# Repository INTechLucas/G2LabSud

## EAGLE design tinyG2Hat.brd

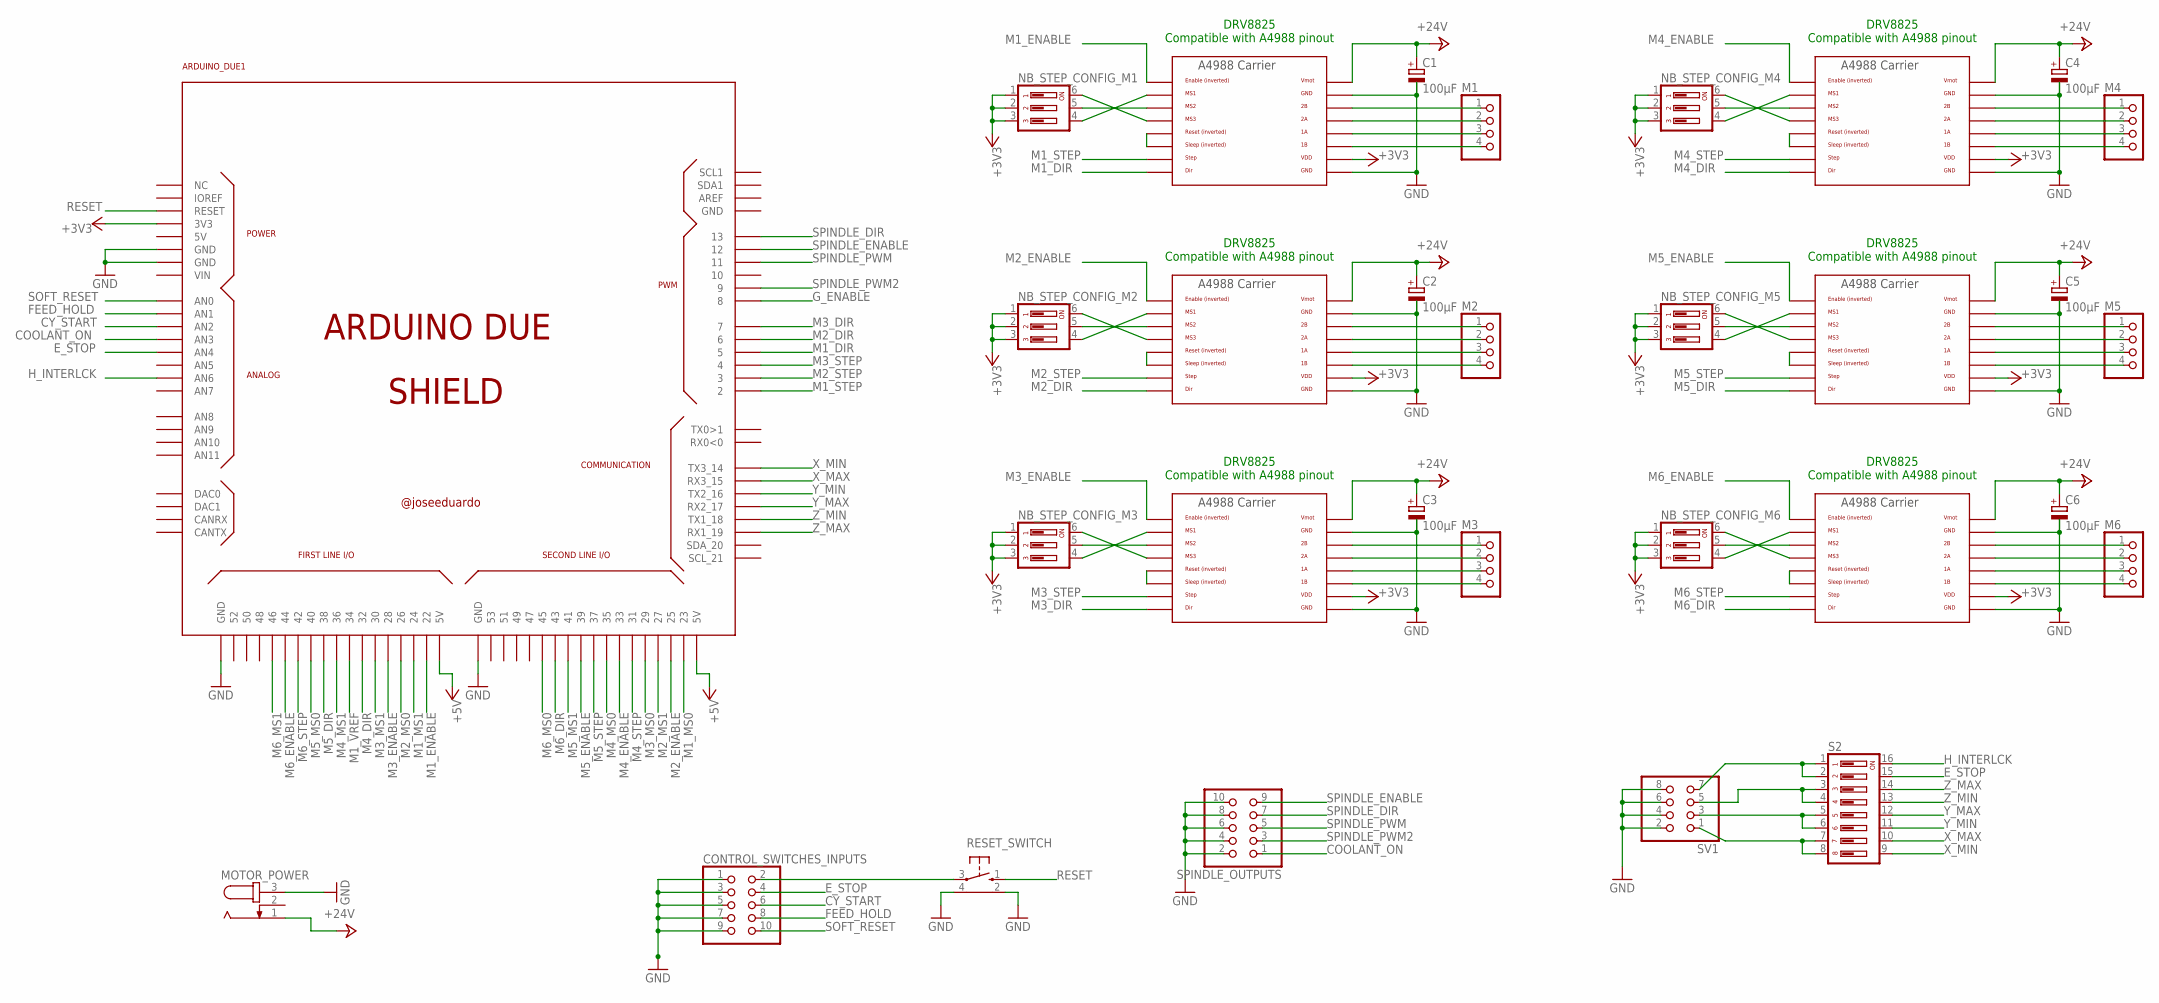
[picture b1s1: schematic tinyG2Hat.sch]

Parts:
ARDUINO_DUE1: ARDUINO_DUE_SHIELD_NOSPI
C1, C2, C3, C4, C5, C6: 100µF; E3,5-8
CONTROL_SWITCHES_INPUTS: PINHD-2X5; 2X05
M1, M2, M3, M4, M5, M6: PINHD-1X4; 1X04
MOTOR_POWER: RAPC7120; RAPC712
NB_STEP_CONFIG_M1, NB_STEP_CONFIG_M2, NB_STEP_CONFIG_M3, NB_STEP_CONFIG_M4, NB_STEP_CONFIG_M5, NB_STEP_CONFIG_M6: DIP03YL
RESET_SWITCH: 10-XX-RPAD; B3F-10XX-RPAD
S2: DIP08YL
SPINDLE_OUTPUTS: PINHD-2X5; 2X05
SV1: PINHD-2X4; 2X04
U$1, U$2, U$3, U$4, U$5, U$6: A4988BREAKOUT

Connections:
+3V3: ARDUINO_DUE1.3V3, NB_STEP_CONFIG_M1.1, NB_STEP_CONFIG_M1.2, NB_STEP_CONFIG_M1.3, NB_STEP_CONFIG_M2.1, NB_STEP_CONFIG_M2.2, NB_STEP_CONFIG_M2.3, NB_STEP_CONFIG_M3.1, NB_STEP_CONFIG_M3.2, NB_STEP_CONFIG_M3.3, NB_STEP_CONFIG_M4.1, NB_STEP_CONFIG_M4.2, NB_STEP_CONFIG_M4.3, NB_STEP_CONFIG_M5.1, NB_STEP_CONFIG_M5.2, NB_STEP_CONFIG_M5.3, NB_STEP_CONFIG_M6.1, NB_STEP_CONFIG_M6.2, NB_STEP_CONFIG_M6.3, U$1.VDD, U$2.VDD, U$3.VDD, U$4.VDD, U$5.VDD, U$6.VDD
+5V: ARDUINO_DUE1.5V0_1 (5V), ARDUINO_DUE1.5V0_2 (5V)
+24V: C1.+, C2.+, C3.+, C4.+, C5.+, C6.+, MOTOR_POWER.1, U$1.VMOT, U$2.VMOT, U$3.VMOT, U$4.VMOT, U$5.VMOT, U$6.VMOT
COOLANT_ON: ARDUINO_DUE1.A3 (AN3), SPINDLE_OUTPUTS.1
CY_START: ARDUINO_DUE1.A2 (AN2), CONTROL_SWITCHES_INPUTS.6
E_STOP: ARDUINO_DUE1.A4 (AN4), CONTROL_SWITCHES_INPUTS.4, S2.15
FEED_HOLD: ARDUINO_DUE1.A1 (AN1), CONTROL_SWITCHES_INPUTS.8
GND: ARDUINO_DUE1.GND, ARDUINO_DUE1.GND_1 (GND), ARDUINO_DUE1.GND_2 (GND), ARDUINO_DUE1.GND_3 (GND), C1.-, C2.-, C3.-, C4.-, C5.-, C6.-, CONTROL_SWITCHES_INPUTS.1, CONTROL_SWITCHES_INPUTS.3, CONTROL_SWITCHES_INPUTS.5, CONTROL_SWITCHES_INPUTS.7, CONTROL_SWITCHES_INPUTS.9, MOTOR_POWER.3, RESET_SWITCH.2 (GND1), RESET_SWITCH.4 (GND2), SPINDLE_OUTPUTS.2, SPINDLE_OUTPUTS.4, SPINDLE_OUTPUTS.6, SPINDLE_OUTPUTS.8, SPINDLE_OUTPUTS.10, SV1.2, SV1.4, SV1.6, SV1.8, U$1.GND, U$1.GND@0 (GND), U$2.GND, U$2.GND@0 (GND), U$3.GND, U$3.GND@0 (GND), U$4.GND, U$4.GND@0 (GND), U$5.GND, U$5.GND@0 (GND), U$6.GND, U$6.GND@0 (GND)
G_ENABLE: ARDUINO_DUE1.8
H_INTERLCK: ARDUINO_DUE1.A6 (AN6), S2.16
M1_DIR: ARDUINO_DUE1.5, U$1.DIR
M1_ENABLE: ARDUINO_DUE1.22, U$1.EN
M1_MS0: ARDUINO_DUE1.23
M1_MS1: ARDUINO_DUE1.24
M1_STEP: ARDUINO_DUE1.2, U$1.STEP
M1_VREF: ARDUINO_DUE1.34
M2_DIR: ARDUINO_DUE1.6, U$2.DIR
M2_ENABLE: ARDUINO_DUE1.25, U$2.EN
M2_MS0: ARDUINO_DUE1.26
M2_MS1: ARDUINO_DUE1.27
M2_STEP: ARDUINO_DUE1.3, U$2.STEP
M3_DIR: ARDUINO_DUE1.7, U$3.DIR
M3_ENABLE: ARDUINO_DUE1.28, U$3.EN
M3_MS0: ARDUINO_DUE1.29
M3_MS1: ARDUINO_DUE1.30
M3_STEP: ARDUINO_DUE1.4, U$3.STEP
M4_DIR: ARDUINO_DUE1.32, U$4.DIR
M4_ENABLE: ARDUINO_DUE1.33, U$4.EN
M4_MS0: ARDUINO_DUE1.35
M4_MS1: ARDUINO_DUE1.36
M4_STEP: ARDUINO_DUE1.31, U$4.STEP
M5_DIR: ARDUINO_DUE1.38, U$5.DIR
M5_ENABLE: ARDUINO_DUE1.39, U$5.EN
M5_MS0: ARDUINO_DUE1.40
M5_MS1: ARDUINO_DUE1.41
M5_STEP: ARDUINO_DUE1.37, U$5.STEP
M6_DIR: ARDUINO_DUE1.43, U$6.DIR
M6_ENABLE: ARDUINO_DUE1.44, U$6.EN
M6_MS0: ARDUINO_DUE1.45
M6_MS1: ARDUINO_DUE1.46
M6_STEP: ARDUINO_DUE1.42, U$6.STEP
unnamed: NB_STEP_CONFIG_M1.6, U$1.MS3
unnamed: NB_STEP_CONFIG_M1.5, U$1.MS2
unnamed: NB_STEP_CONFIG_M1.4, U$1.MS1
unnamed: U$1.RST, U$1.SLP (SLEEP)
unnamed: M1.1, U$1.2B
unnamed: M1.2, U$1.2A
unnamed: M1.3, U$1.1A
unnamed: M1.4, U$1.1B
unnamed: NB_STEP_CONFIG_M2.5, U$2.MS2
unnamed: U$2.RST, U$2.SLP (SLEEP)
unnamed: M2.1, U$2.2B
unnamed: M2.2, U$2.2A
unnamed: M2.3, U$2.1A
unnamed: M2.4, U$2.1B
unnamed: NB_STEP_CONFIG_M2.6, U$2.MS3
unnamed: NB_STEP_CONFIG_M2.4, U$2.MS1
unnamed: NB_STEP_CONFIG_M3.5, U$3.MS2
unnamed: U$3.RST, U$3.SLP (SLEEP)
unnamed: M3.1, U$3.2B
unnamed: M3.2, U$3.2A
unnamed: M3.3, U$3.1A
unnamed: M3.4, U$3.1B
unnamed: NB_STEP_CONFIG_M3.6, U$3.MS3
unnamed: NB_STEP_CONFIG_M3.4, U$3.MS1
unnamed: NB_STEP_CONFIG_M4.5, U$4.MS2
unnamed: U$4.RST, U$4.SLP (SLEEP)
unnamed: M4.1, U$4.2B
unnamed: M4.2, U$4.2A
unnamed: M4.3, U$4.1A
unnamed: M4.4, U$4.1B
unnamed: NB_STEP_CONFIG_M4.6, U$4.MS3
unnamed: NB_STEP_CONFIG_M4.4, U$4.MS1
unnamed: NB_STEP_CONFIG_M5.5, U$5.MS2
unnamed: U$5.RST, U$5.SLP (SLEEP)
unnamed: M5.1, U$5.2B
unnamed: M5.2, U$5.2A
unnamed: M5.3, U$5.1A
unnamed: M5.4, U$5.1B
unnamed: NB_STEP_CONFIG_M5.6, U$5.MS3
unnamed: NB_STEP_CONFIG_M5.4, U$5.MS1
unnamed: NB_STEP_CONFIG_M6.5, U$6.MS2
unnamed: U$6.RST, U$6.SLP (SLEEP)
unnamed: M6.1, U$6.2B
unnamed: M6.2, U$6.2A
unnamed: M6.3, U$6.1A
unnamed: M6.4, U$6.1B
unnamed: NB_STEP_CONFIG_M6.6, U$6.MS3
unnamed: NB_STEP_CONFIG_M6.4, U$6.MS1
unnamed: S2.1, S2.2, SV1.7
unnamed: CONTROL_SWITCHES_INPUTS.2, RESET_SWITCH.3
unnamed: S2.3, S2.4, SV1.5
unnamed: S2.5, S2.6, SV1.3
unnamed: S2.7, S2.8, SV1.1
RESET: ARDUINO_DUE1.RESET, RESET_SWITCH.1 (S)
SOFT_RESET: ARDUINO_DUE1.A0 (AN0), CONTROL_SWITCHES_INPUTS.10
SPINDLE_DIR: ARDUINO_DUE1.13, SPINDLE_OUTPUTS.7
SPINDLE_ENABLE: ARDUINO_DUE1.12, SPINDLE_OUTPUTS.9
SPINDLE_PWM: ARDUINO_DUE1.11, SPINDLE_OUTPUTS.5
SPINDLE_PWM2: ARDUINO_DUE1.9, SPINDLE_OUTPUTS.3
X_MAX: ARDUINO_DUE1.15 (RX3_15), S2.10
X_MIN: ARDUINO_DUE1.14 (TX3_14), S2.9
Y_MAX: ARDUINO_DUE1.17 (RX2_17), S2.12
Y_MIN: ARDUINO_DUE1.16 (TX2_16), S2.11
Z_MAX: ARDUINO_DUE1.19 (RX1_19), S2.14
Z_MIN: ARDUINO_DUE1.18 (TX1_18), S2.13

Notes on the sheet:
DRV8825 Compatible with A4988 pinout

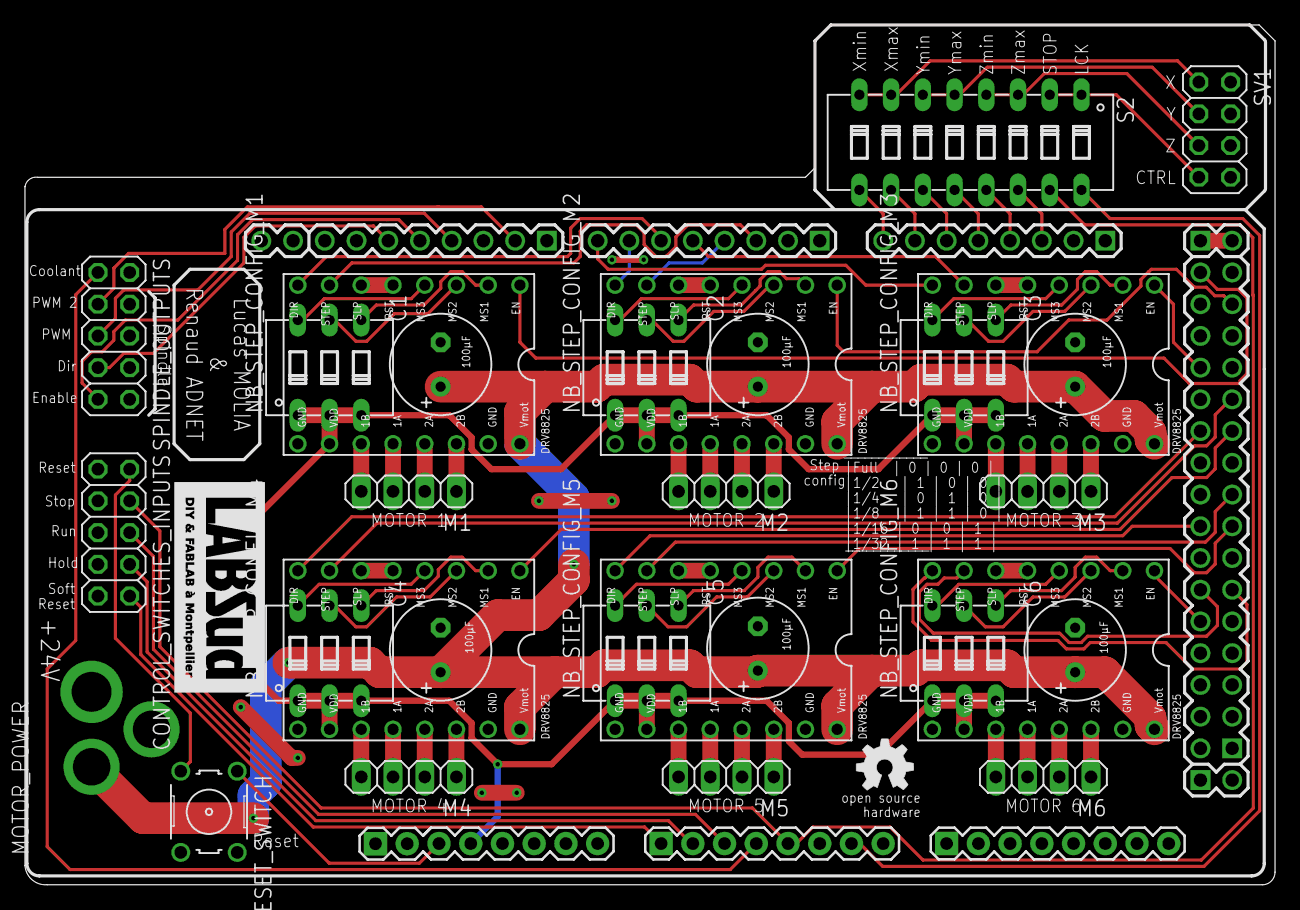
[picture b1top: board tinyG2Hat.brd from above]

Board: 2 copper layers, 100.1 x 68.8 mm, 33 parts (0 on the bottom side), 92 nets.

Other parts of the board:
U$7: OPEN_HARDWARE_5MM
U$8: LABSUD_15MM

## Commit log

2018-07-18 6 moteurs placés dans le schematic
2018-07-18 Ajout des entrée capteurs fin course et sortie spindle dans le schematic
2018-07-19 Ajout des commandes manuelles
2018-07-19 Routage du Spindle, M1 et M2
2018-07-19 Routage de M3 et des entrées avec leur switch de config
2018-07-19 Routage de M4
2018-07-19 Routage de M5 et M6. 6 drivers, spindle, 4 capteurs routés
2018-07-19 Routage de base terminé
2018-07-23 Début de la sérigraphie
2018-07-23 Sérigraphie finie
2018-07-23 Correctifs sérigraphie
2018-07-24 Finalisation
